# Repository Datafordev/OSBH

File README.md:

#Open Source Beehives Project #
#Alpha Sensor Kit #
====================================================

Developed for Open Source Beehives Project
http://opensourcebeehives.net

The master branch for the firmware is being rewritten.
The old Code is saved to the Alpha_Kit_02 branch.

**License**
--------
This application contains several libraries and files.  Check the comments section of the .cpp and .h files for the specific details on the licenses.

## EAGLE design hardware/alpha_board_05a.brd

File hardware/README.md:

#Open Source Beehives Project #
#Alpha Sensor Kit #
====================================================

Developed for Open Source Beehives Project
http://opensourcebeehives.net

**Hardware AlphaKit V.04**

We designed a shield for the Particle Core/Photon where you can attach following sensors:

- 2x Temp DS18B20
- 2x Temp and Humidity DHT22
- 2x Audio sensor (like audio breakout from SparkFun - more details in audio_sensor)
- 1x Weight sensor

There's also an micro SD Card Slot and a RTC Clock Device installed to be able to work in offline areas.

You'll find a Bill of materials list in bom.ods

**Important for producing the PCB**
It's a doublesided PCB so you need to make sure that pins and vias are through contacted!

**License**
--------
GPL

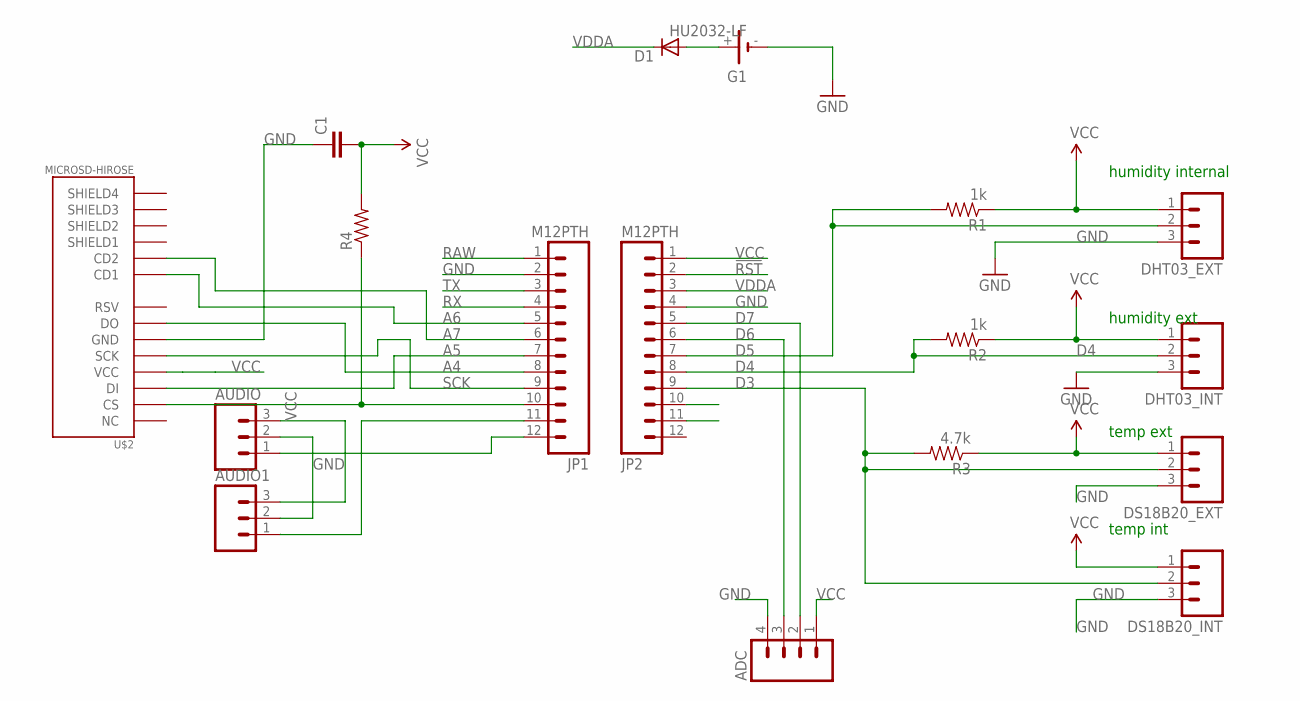
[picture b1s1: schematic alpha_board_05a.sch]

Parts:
ADC: M04LOCK_LONGPADS; 1X04_LOCK_LONGPADS
AUDIO, AUDIO1: M03LOCK; 1X03_LOCK
C1: CAP1206; 1206
D1: DIODE-SOD323-W; SOD323-W
DHT03_EXT, DHT03_INT: M03LOCK; 1X03_LOCK
DS18B20_EXT, DS18B20_INT: M03LOCK; 1X03_LOCK
G1: HU2032-LF
JP1, JP2: M12PTH; 1X12-SMALL-PADS
R1, R2: 1k; 1206
R3: 4.7k; 1206
R4: RESISTOR1206; 1206
U$2: MICROSD-HIROSE; MICROSD_HOLDER-HIROSE-DM3AT

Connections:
!RST: JP2.2
A4: JP1.8, U$2.DAT0 (DO)
A5: JP1.7, U$2.CMD (DI)
A6: JP1.5, U$2.CD1
A7: JP1.6, U$2.CD2
D3: DS18B20_EXT.2, DS18B20_INT.2, JP2.9, R3.2
D4: DHT03_INT.2, JP2.8, R2.2
D5: DHT03_EXT.2, JP2.7, R1.2
D6: ADC.3, JP2.6
D7: ADC.2, JP2.5
GND: ADC.4, AUDIO.2, AUDIO1.2, C1.1, DHT03_EXT.3, DHT03_INT.3, DS18B20_EXT.3, DS18B20_INT.3, G1.-, JP1.2, JP2.4, U$2.VSS (GND)
unnamed: JP1.10, R4.1, U$2.DAT3 (CS)
unnamed: AUDIO.1, JP1.12
unnamed: D1.A, G1.+
unnamed: AUDIO1.1, JP1.11
RAW: JP1.1
RX: JP1.4
SCK: JP1.9, U$2.CLK (SCK)
TX: JP1.3
VCC: ADC.1, AUDIO.3, AUDIO1.3, C1.2, DHT03_EXT.1, DHT03_INT.1, DS18B20_EXT.1, DS18B20_INT.1, JP2.1, R1.1, R2.1, R3.1, R4.2, U$2.VDD (VCC)
VDDA: D1.C, JP2.3

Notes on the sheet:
humidity internal
temp int
temp ext
humidity ext

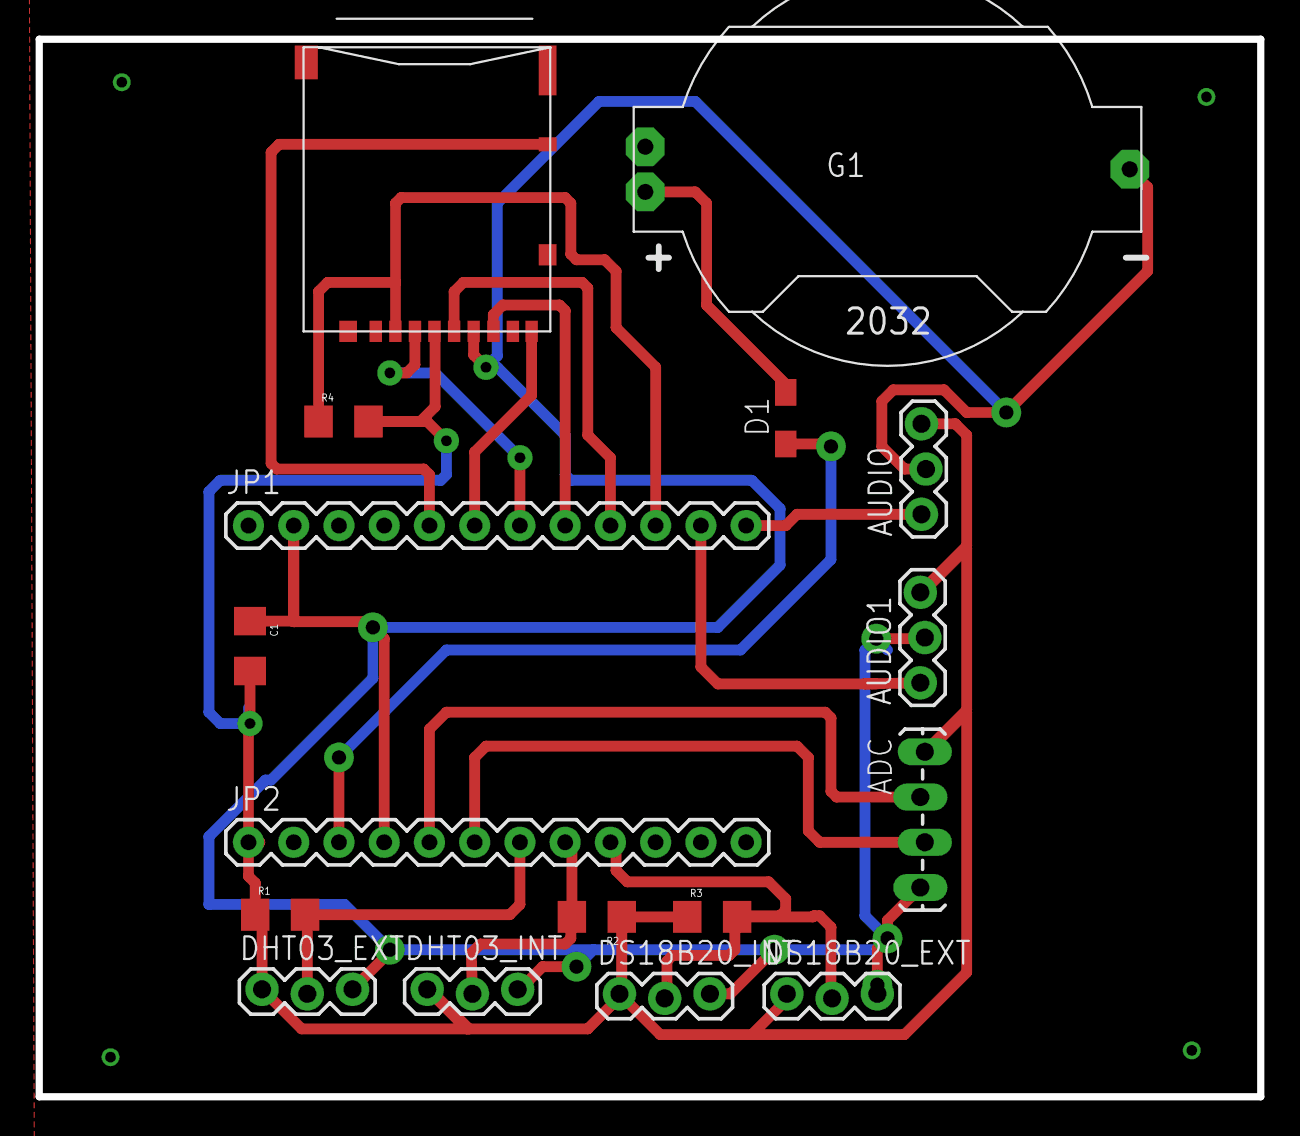
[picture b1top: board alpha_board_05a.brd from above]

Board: 2 copper layers, 68.6 x 59.4 mm, 17 parts (0 on the bottom side), 17 nets.

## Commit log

2015-03-28 updated components for the kit
2015-05-06 preparing for rewrite. deleting Piettetech
2015-05-10 add DHT and dallas sensor libs; move libs to subdirectory; change includes
2015-05-10 add minimal sketch (no sensors yet)
2015-05-11 deleted Piettech in DSX and few changes for new Adafruit Sensor
2015-05-22 add new DSX_Unified wrapper for modified DSX_Sensor class
2015-05-22 re-add DHT22 sensors as well; respect sensors' minimum read intervals
2015-05-22 wrap sensors in a sensor_array class, reorganize files OSBH.cpp and OSBH.ino were causing linker name conflicts
2015-06-02 minor improvements, e.g. more consistent naming
2015-06-04 re-add SD card functionality
2015-06-06 use char arrays instead of String for timestamp and output to avoid memory fragmentation
2015-06-06 add TEMP/HUM suffix to DHT* sensor names
2015-06-07 add audio code from last firmware rev (no changes)
2015-06-08 fix bug in DHT library to ensure that failed readings always return NAN
2015-06-29 hardware added
2015-06-29 bom added
2015-07-06 make output format more configurable, fix warning in DHT_U library
2015-07-06 use SD CD pin to handle card removal/re-insertion
2015-07-17 hardware update, new RTC chip, smaller footprint
2015-08-27 update firmware for Particle Photon
2015-11-19 update firmware to track changes in Particle firmware
2015-12-01 audio SD Card output added
2016-01-28 04 update, SD pin detect, audio output, mqtt database connection, RTC
2016-01-28 new PCB design without external RTC, thanks Angel M!
2016-02-09 few bug changes

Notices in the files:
parts and their libraries:
SparkFun: Licensing: CC v3.0 Share-Alike You are welcome to use this library for commercial purposes.
SparkFun-Connectors: Licensing: Creative Commons ShareAlike 4.0 International - https://creativecommons.org/licenses/by-sa/4.0
